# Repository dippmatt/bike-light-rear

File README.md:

# bike-light-rear

High-visibility rear bicycle light controlled from an ANT+ bike computer (ANT+ Bike Lights profile), featuring smart motion detection, ambient light sensing, and efficient single-cell Li-ion power management. Designed for hybrid assembly (pick-and-place for 0402/0603 passives, hand-soldering for connectors and high-value components).

## Hardware architecture

### Compute & wireless
- **BL653 module** (453-00039R) – Nordic nRF52833 SoC with integrated PCB trace antenna, ANT/Bluetooth radio, and 64 MHz Arm Cortex-M4F (the firmware uses the ANT SoftDevice, so the radio runs ANT+)
- **Programming** – 2×3 1.27mm SWD header for firmware flashing and debugging
- **System power** – 2.7V from NPM1100 buck regulator optimized for 90-95% battery capacity utilization (3.11V cutoff)

### Sensors (I2C bus @ 2.7V)
- **LIS3DH accelerometer** – 3-axis motion detection (braking / fall detection) for brake/acceleration events, configurable thresholds, interrupt-driven
- **OPT3001 light sensor** – 0.01-83k lux range with human-eye spectral matching for automatic brightness control and day/night mode switching

### High-power LED driver
- **Cree XP-E2** (XPEBRD-L1-0000-00801) – 625nm Red emitter driven at 500mA via PAM2804 step-down constant-current driver
- **Control** – PWM dimming via BL653 GPIO with 100kΩ pull-down for safe default-off state

### Power subsystem
- **Battery** – Single 18350 Li-ion cell (Vapcell 1100mAh, unprotected), 3.11-4.2V operating range
- **Charging** – USB-C PD sink (5.1kΩ CC resistors), NPM1100 linear charger @ 400mA (0Ω ICHG resistor), 4.2V termination
- **Protection** – DW01A IC with dual AO3400A N-channel MOSFETs (drain-to-drain configuration) for over-voltage (4.3V), under-voltage (2.5V), and over-current (>2A) protection
- **Buck regulator** – NPM1100 internal 2.7V @ 150mA output
- **Status monitoring** – CHG and ERR signals routed to BL653 GPIO for firmware-based charge status indication
- **NTC disable** – Thermal monitoring disabled via 10kΩ resistor from NTC pin to AVSS (GND)

### PCB specifications
- **Design tool** – KiCad 9.0 (schema version `20250114`)
- **Test points** – Critical nets labeled for bring-up and debugging (+BATT, +VSYS, +VDD_nRF, GND, I2C_SDA, I2C_SCL)

### Hardware photos

Assembled PCB on the 18350 battery holder (angled view).

Top of the populated PCB: BL653 (nRF52833), USB-C, tactile switch, RGB status LED, SWD header (J2), and I2C test point pads for the accelerometer and ambient light sensor.

Front of the 3D-printed enclosure with the Cree red main LED and status indicator.

Side of the enclosure showing the USB charge port.

## Repository layout
- `hardware/` – KiCad project, fabrication-toolkit config, custom libs (`kicad_symbols/`, `kicad_footprints/`, `kicad_3d_models/`), datasheets (markdown format), and generated BOM
- `software/rear_light_ant/` – rear light firmware (bare metal on the ANT SoftDevice S212), including Smart Mode, ANT+ bike light control, charging/idle state, and low-power sleep
- `software/rear_light_peripheral/` – the previous Zephyr/BLE rear light firmware, kept as reference until the physical checks of the ANT+ firmware are done
- `software/front_light_central/` – proof-of-concept BLE central/front-light firmware (experimental). It controlled the BLE rear light and does not work with the ANT+ rear light
- `software/` *(other folders)* – development history and experiments (central/peripheral prototypes, refactors, test projects)
- `docs/` – photos, rendered schematics, mechanical notes, and user-facing manuals
- `LICENSE` – GPLv3 with NonCommercial clause

## Hardware workflow
1. Install KiCad 9.0 or newer.
2. Install the [JLCPCB Fabrication Toolkit](https://github.com/bennymeg/Fabrication-Toolkit) to be able to export the design in the correct format for JLCPCBs [Design For Manufacturing (DFM) Tool](https://jlcdfm.com/).
3. Open `hardware/kicad_project/RearLight.kicad_pro` to access the schematic and PCB.
4. Run ERC/DRC before layout edits; generated artifacts (Gerbers, pick-and-place, STEP export) go to `hardware/kicad_project/production`, which is gitignored and intentionally kept out of releases.
5. Note: Components marked DNP (Do Not Populate) in fabrication files are intended for hand-soldering to minimize assembly costs.

## Firmware

The rear light firmware (`software/rear_light_ant/`) runs bare metal on the **ANT SoftDevice S212 7.0.1** of the **nRF52833 (BL653 module)**. ANT SoftDevices are not supported by Zephyr or the nRF Connect SDK, so it uses a plain Makefile with the compiler of an nRF Connect SDK toolchain installation (v3.1.1) and the register headers of its nrfx. It implements the lighting control with three light modes and is controlled by an ANT+ bike computer through the ANT+ Bike Lights profile (tested with a Wahoo ELEMNT BOLT v2).

### Features
- **Three light modes**: Steady, Flash (double flash) and Smart, plus Off from the bike computer
- **Smart Mode**: Adaptive brightness based on braking detection and ambient light
- **Braking Detection**: Automatic peak brightness boost during deceleration
- **Ambient Light Sensing**: Adjusts brightness for day/night conditions
- **Parking and auto-on**: when the bike stands still for 2.5 minutes Smart parks (LED off, short status pulse) and switches itself back on when the bike moves
- **Power Management**: Low-battery indication and automatic shut-off at low voltage, USB-C charging indication
- **ANT+ control**: state, battery and mode of the light on the bike computer, mode changes from the bike computer

For complete operating instructions and technical details, see the **[Rear light User Manual](software/rear_light_ant/MANUAL.md)**; the behaviour is specified in [SPEC.md](software/rear_light_ant/SPEC.md).

The **front light** uses the same board with a white LED and the same firmware source, built as a variant (`make LIGHT=front`): Smart, Standard (30 %) and Bright (80 %), see the **[Front light User Manual](software/rear_light_ant/MANUAL_FRONT.md)**. The BLE front light firmware in `software/front_light_central/` is superseded.

### Firmware environment setup
1. Install the [nRF Command Line Tools](https://www.nordicsemi.com/Products/Development-tools/nrf-command-line-tools) for access to `nrfjprog` and a J-Link.
2. Install the **nRF Connect SDK toolchain v3.1.1** (nRF Connect for VS Code, Toolchain Manager). Only its GNU Arm compiler and the nrfx register headers are used.
3. Put the ANT SoftDevice archive `ANT_s212_nrf52_7.0.1.zip` (from the Garmin/ANT downloads) into `software/ant_source/SoftDevices_Current_Items/`. The folder is gitignored: the ANT+ documents and SoftDevice files must not be redistributed.
4. `cd software/rear_light_ant && make test && make flash` (front light: `make LIGHT=front flash`; see its [README](software/rear_light_ant/README.md) for options, bench tools and the licence key).

The previous Zephyr firmware in `software/rear_light_peripheral/` is built with the nRF Connect for VS Code extension as before (nRF Connect Bare Metal SDK v0.9.0 and toolchain v3.1.1).

Note 1: Device flashing using WSL2  
To connect a J-Link debugger to a WSL instance:
- Open a Windows PowerShell terminal and run:
- `usbipd list`
- `usbipd bind --busid <J-Link BusID>`
- `usbipd attach --wsl --busid <J-Link BusID>`

Note 2: Device does not show up under “Connected Devices” in the nRF Connect VS Code extension
- Install [nRF-Util](https://www.nordicsemi.com/Products/Development-tools/nRF-Util)
- Make nrfutil executable using `chmod +x nrfutil`
- Move the nrfutil executable to a directory in the system $PATH (e.g. /usr/bin)
- Install the _device_ package for nrfutil using `nrfutil install device`
- Restart VSCode. Your device should now show up under _Connected Devices_ in nRF Connect  

## License
This hardware is released under **GPLv3 + NonCommercial**. You may copy, modify, and share for non-commercial use as long as derivatives retain the same license and attribution. See `LICENSE` for full terms.

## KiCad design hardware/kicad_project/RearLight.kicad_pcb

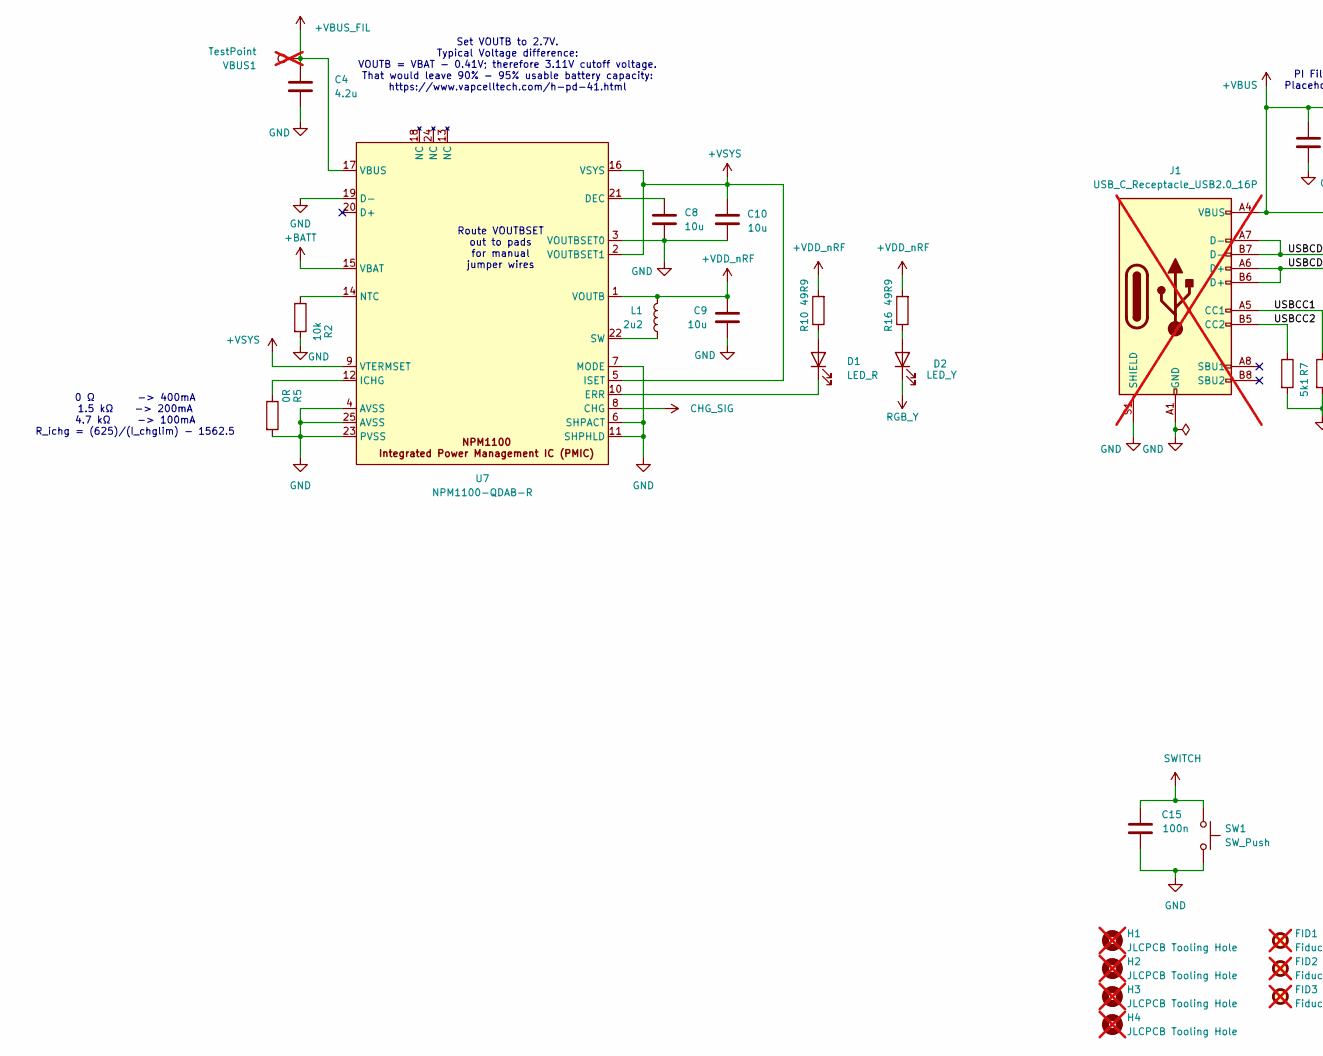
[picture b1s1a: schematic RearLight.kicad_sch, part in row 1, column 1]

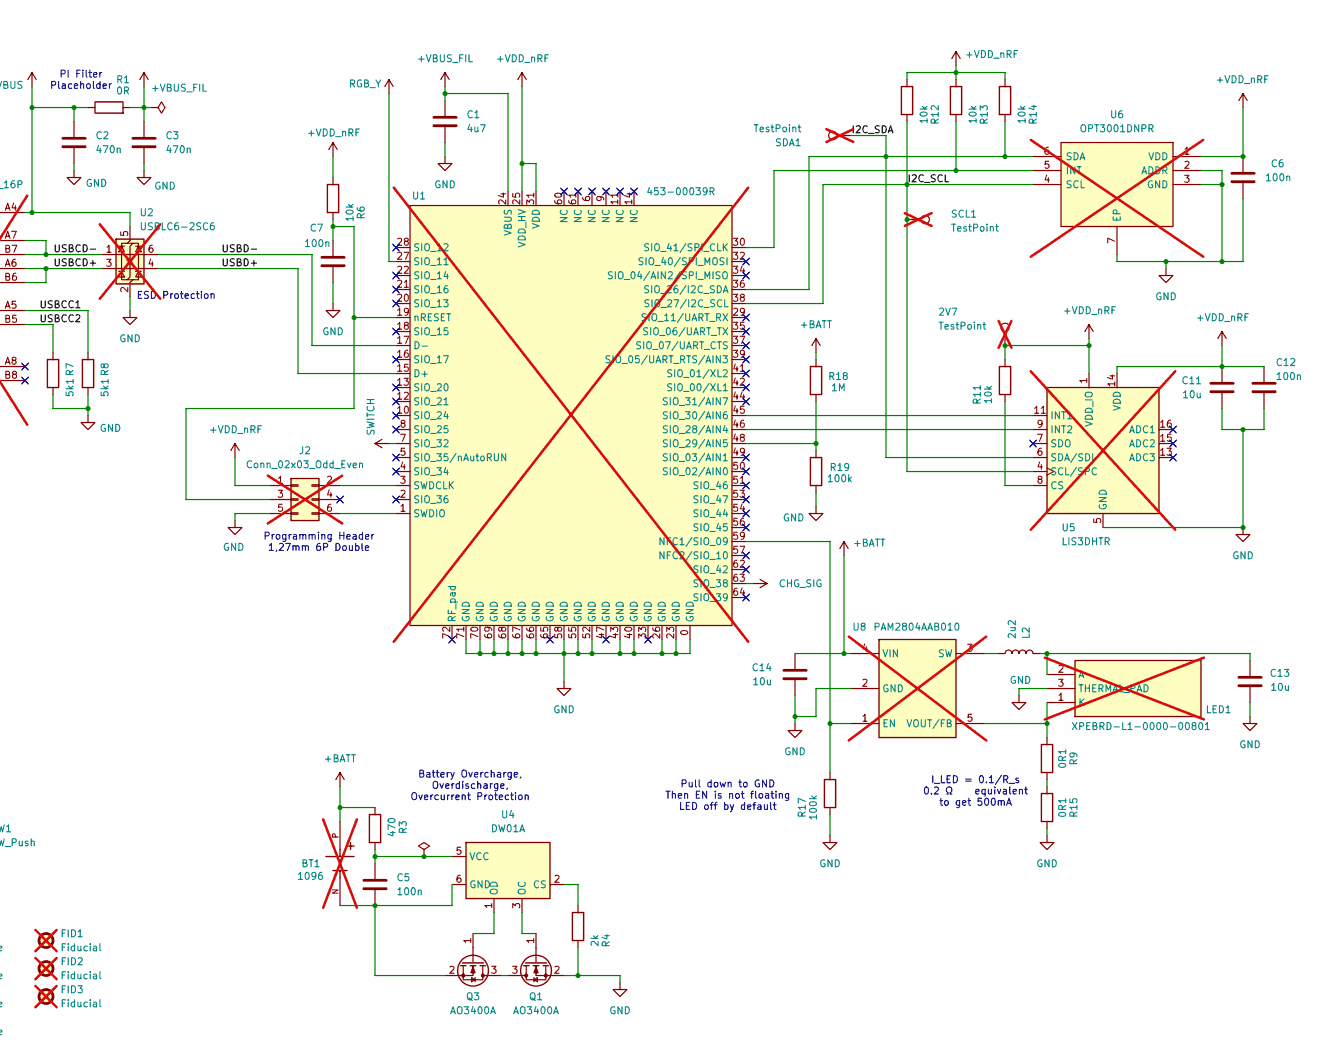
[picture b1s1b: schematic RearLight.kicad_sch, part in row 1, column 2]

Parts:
2V7: TestPoint; TestPoint_Pad_D1.0mm; not fitted
BT1: 1096; BAT_1096_holes_slim; PARTREV A; DigiKey_Part_Number 36-1096-ND; not fitted
C1: 4u7; C_0805_2012Metric; LCSC C1779
C2, C3: 470n; C_0603_1608Metric_NO_SILK; LCSC C1623
C4: 4.2u; C_0805_2012Metric; LCSC C377773
C5, C6, C7, C12, C15: 100n; C_0805_2012Metric; LCSC C28233
C8, C9, C10, C11, C13, C14: 10u; C_0805_2012Metric; LCSC C15850
D1: LED_R; LED_0603_1608Metric; LCSC C2286
D2: LED_Y; LED_0805_2012Metric; LCSC C2296
FID1, FID2, FID3: Fiducial; Fiducial_1mm_Mask2mm; not fitted
H1, H2, H3, H4: JLCPCB Tooling Hole; ToolingHole_1.152mm; not fitted
J1: USB_C_Receptacle_USB2.0_16P; USB_C_Receptacle_GCT_USB4105-xx-A_16P_TopMnt_Horizontal_wid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; Manufacturer Part Number USB4105-GF-A-060; LCSC C3025063; not fitted
J2: Conn_02x03_Odd_Even; PinHeader_2x03_P1.27mm_Vertical; not fitted
L1, L2: 2u2; L_0805_2012Metric; LCSC C1043
LED1: XPEBRD-L1-0000-00801; XPEWHTL1000000E01; Manufacturer_Part_Number XPEBRD-L1-0000-00801; LCSC C5364087; not fitted
Q1, Q3: AO3400A; SOT-23; LCSC C20917
R1, R5: 0R; R_0603_1608Metric_NO_SILK; LCSC C21189
R2, R6, R12, R13, R14: 10k; R_0402_1005Metric_NO_SILK; Manufacturer Part Number 0402WGF1002TCE; LCSC C25744
R3: 470; R_0402_1005Metric_NO_SILK; Manufacturer Part Number 0402WGF4700TCE; LCSC C25117
R4: 2k; R_0402_1005Metric_NO_SILK; Manufacturer Part Number 0402WGF2001TCE; LCSC C4109
R7, R8: 5k1; R_0402_1005Metric_NO_SILK; Manufacturer Part Number 0402WGF5101TCE; LCSC C25905
R9, R15: 0R1; R_1206_3216Metric; Manufacturer Part Number 1206W4F100LT5E; LCSC C25334
R10, R16: 49R9; R_0402_1005Metric_NO_SILK; Manufacturer Part Number 0402WGF499JTCE; LCSC C25120
R11: 10k; R_0603_1608Metric_NO_SILK; Manufacturer Part Number 0603WAF1002T5E; LCSC C25804
R17, R19: 100k; R_0402_1005Metric_NO_SILK; Manufacturer Part Number 0402WGF1003TCE; LCSC C25741
R18: 1M; R_0402_1005Metric_NO_SILK; Manufacturer Part Number 0402WGF1004TCE; LCSC C26083
SCL1: TestPoint; TestPoint_Pad_D1.0mm; not fitted
SDA1: TestPoint; TestPoint_Pad_D1.0mm; not fitted
SW1: SW_Push; SW_TS-1088-AR02016; LCSC C720477
U1: 453-00039R; Laird_BL653; LCSC C6421506; not fitted
U2: USBLC6-2SC6; SOT-23-6; Manufacturer Part Number USBLC6-2SC6; LCSC C7519; not fitted
U4: DW01A; SOT-23-6; LCSC C18164398
U5: LIS3DHTR; LGA-16_3x3mm_P0.5mm_LayoutBorder3x5y; Manufacturer Part Number LIS3DHTR; LCSC C15134; not fitted
U6: OPT3001DNPR; SON65P200X200X65-7N-D; Mouser Part Number 595-OPT3001DNPR; not fitted
U7: NPM1100-QDAB-R; QFN50P400X400X90-25N-D; LCSC C5833729
U8: PAM2804AAB010; SOT95P280X100-5N; LCSC C71463; not fitted
VBUS1: TestPoint; TestPoint_Pad_D1.0mm; not fitted

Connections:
+BATT: BT1.P, C14.1, R3.1, R18.1, U7.15 (VBAT), U8.4 (VIN)
+VBUS: C2.1, J1.A4 (VBUS), J1.A9 (VBUS), J1.B4 (VBUS), J1.B9 (VBUS), R1.1, U2.5 (VBUS)
+VBUS_FIL: C1.1, C3.1, C4.1, R1.2, U1.24 (VBUS), U7.17 (VBUS), VBUS1.1
+VDD_nRF: 2V7.1, C6.1, C9.1, C11.1, C12.1, J2.1, L1.1, R6.1, R10.2, R11.1, R12.1, R13.1, R14.1, R16.2, U1.25 (VDD_HV), U1.31 (VDD), U5.1 (VDD_IO), U5.14 (VDD), U6.1 (VDD), U7.1 (VOUTB)
+VSYS: C10.1, U7.2 (VOUTBSET1), U7.5 (ISET), U7.9 (VTERMSET), U7.16 (VSYS)
/I2C_SCL: R12.2, SCL1.1, U1.38 (SIO_27/I2C_SCL), U5.4 (SCL/SPC), U6.4 (SCL)
/I2C_SDA: R14.2, SDA1.1, U1.36 (SIO_26/I2C_SDA), U5.6 (SDA/SDI), U6.6 (SDA)
/USBCC1: J1.A5 (CC1), R8.1
/USBCC2: J1.B5 (CC2), R7.1
/USBCD+: J1.A6 (D+), J1.B6 (D+), U2.3 (I/O2)
/USBCD-: J1.A7 (D-), J1.B7 (D-), U2.1 (I/O1)
/USBD+: U1.15 (D+), U2.4 (I/O2)
/USBD-: U1.17 (D-), U2.6 (I/O1)
CHG_SIG: U1.63 (SIO_38), U7.8 (CHG)
GND: C1.2, C2.2, C3.2, C4.2, C6.2, C7.2, C8.2, C9.2, C10.2, C11.2, C12.2, C13.2, C14.2, C15.2, J1.A1 (GND), J1.A12 (GND), J1.B1 (GND), J1.B12 (GND), J1.S1 (SHIELD), J2.5, LED1.3 (THERMAL_PAD), Q1.2 (S), R2.2, R4.2, R5.2, R7.2, R8.2, R15.2, R17.2, R19.2, SW1.2, U1.0 (GND), U1.23 (GND), U1.26 (GND), U1.40 (GND), U1.43 (GND), U1.52 (GND), U1.55 (GND), U1.58 (GND), U1.66 (GND), U1.67 (GND), U1.68 (GND), U1.69 (GND), U1.70 (GND), U1.71 (GND), U2.2 (GND), U5.5 (GND), U5.10 (GND), U5.12 (GND), U6.2 (ADDR), U6.3 (GND), U6.7 (EP), U7.3 (VOUTBSET0), U7.4 (AVSS), U7.6 (SHPACT), U7.7 (MODE), U7.11 (SHPHLD), U7.19 (D-), U7.23 (PVSS), U7.25 (AVSS), U8.2 (GND)
unnamed: D1.2 (A), R10.1
unnamed: D1.1 (K), U7.10 (ERR)
unnamed: D2.2 (A), R16.1
unnamed: J2.2, U1.3 (SWDCLK)
unnamed: C7.1, J2.3, R6.2, U1.19 (nRESET)
unnamed: J2.6, U1.1 (SWDIO)
unnamed: C13.1, L2.1, LED1.2 (A)
unnamed: LED1.1 (K), R9.1, U8.5 (VOUT/FB)
unnamed: Q1.3 (D), Q3.3 (D)
unnamed: Q1.1 (G), U4.3 (OC)
unnamed: Q3.1 (G), U4.1 (OD)
unnamed: BT1.N, C5.2, Q3.2 (S), U4.6 (GND)
unnamed: R9.2, R15.1
unnamed: R17.1, U1.59 (NFC1/SIO_09), U8.1 (EN)
unnamed: U1.46 (SIO_28/AIN4), U5.9 (INT2)
unnamed: R18.2, R19.1, U1.48 (SIO_29/AIN5)
unnamed: U1.45 (SIO_30/AIN6), U5.11 (INT1)
unnamed: R13.2, U1.30 (SIO_41/SPI_CLK), U6.5 (INT)
unnamed: R4.1, U4.2 (CS)
unnamed: C5.1, R3.2, U4.5 (VCC)
unnamed: R11.2, U5.8 (CS)
unnamed: C8.1, U7.21 (DEC)
unnamed: R5.1, U7.12 (ICHG)
unnamed: R2.1, U7.14 (NTC)
unnamed: L1.2, U7.22 (SW)
unnamed: L2.2, U8.3 (SW)
RGB_Y: D2.1 (K), U1.27 (SIO_11)
SWITCH: C15.1, SW1.1, U1.7 (SIO_32)

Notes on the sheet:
0 Ω -> 400mA 1.5 kΩ -> 200mA 4.7 kΩ -> 100mA R_ichg = (625)/(I_chglim) - 1562.5
Programming Header 1,27mm 6P Double
Set VOUTB to 2.7V. Typical Voltage difference: VOUTB = VBAT - 0.41V; therefore 3.11V cutoff voltage. That would leave 90% - 95% usable battery capacity: https://www.vapcelltech.com/h-pd-41.html
Route VOUTBSET out to pads for manual jumper wires
ESD Protection
I_LED = 0.1/R_s 0.2 Ω equivalent to get 500mA
PI Filter Placeholder
Pull down to GND Then EN is not floating LED off by default
Battery Overcharge, Overdischarge, Overcurrent Protection

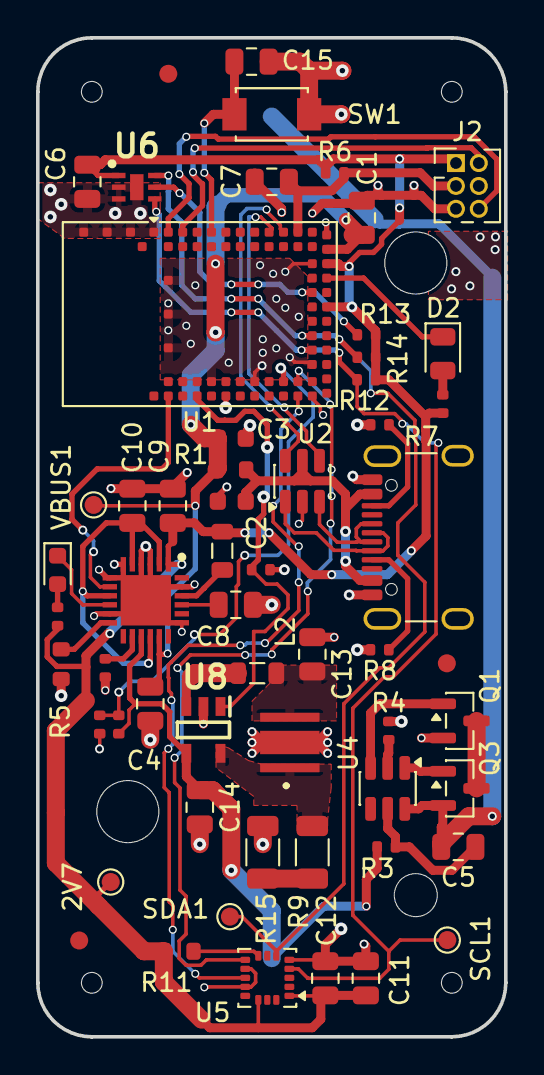
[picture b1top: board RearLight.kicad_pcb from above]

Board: 2 copper layers, 26.0 x 55.5 mm, 63 parts (1 on the bottom side), 43 nets.

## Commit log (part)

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2025-11-07 Added kicad project (schematic)
2025-11-08 Schematic first draft, review needed
2025-11-15 Schematic done; Layout first draft
2025-11-18 Layout 2nd draft
    Todo: increase via size
2025-11-18 DFM design overhaul
2025-11-19 Broad hardware documentation in readme
2025-11-19 Added correct tooling holes for JLCPCB assembly
2025-11-19 better placement & silkscreen for DFM
2025-11-19 Added total cost calculation spredsheet
2025-11-19 Added 100k pulldown to LED driver EN
2025-11-20 Production Version 1.0
    Moved red LED to NPM1100
2025-11-21 Updated actual cost of oredered parts.
2025-12-11 updated board thickness to 1.6 mm
    The board was manufactured with 1.6 mm board thickness accidentaly.
    To reflect this, updated the kicad project as well.
2025-12-23 Initial nRF Connect software setup
2025-12-24 Simple LED on/off control w/ 50% PWM duty cycle
2025-12-24 3-mode light toggle: off, 50%, 100%
2025-12-25 Refactor & Add strict compiler warnings
    - Moved button_control functionallity to main.
    - Enable -Wall, -Wextra, and -Werror for stricter code quality
    - Link math library (-lm) for future sensor calculations
2025-12-25 Added temperature sensor
2025-12-27 Added accellerometer sensor
2025-12-27 Added DEBUG parameter to exclude printing
2025-12-27 Fixed too fast PWM frequency
    100us period got filtered out by the series inductor with the power LED
    1ms period is appropriate for dimming functions.
2025-12-27 Updated license headers
2025-12-31 Added braking and low ambient light detection.
2026-01-04 Added Sleep mode & Smart mode
    Sleep mode uses ~20 uA (device off) w/ wake button interrupt.
    Smart Mode controls the led brightness based on braking deceleration & abient light.
2026-01-04 Code refactored for structure
2026-01-08 Refactored state machine
2026-01-08 Code simplification according to comments attached
    MAIN.C
    Constant definitions
    - Get the status led integer definition from DT
    X - Set the PWM width for the Status Led to 500ms --> rename TIMER_INTERVAL_MS to STATUS_TIMER_INTERVAL
    - Get the device tree specifications (pointer to gpio_dt_spec) from the status led
    X - Define a k_timer led_timer for the status led --> rename to status_led_timer
2026-01-09 Added double flash to flash mode
2026-01-16 Added first bluetooth sync function
2026-01-16 Added short and long press detection
2026-01-21 State machine to OFF after 10s of button inactivity
2026-01-26 Non working BLE setup
2026-01-26 Integrated seperate bluetooth central & peripheral applications
2026-01-30 Added correct BLE functionality
    A bug that prevents the peripheral to enter sleep mode after smart mode exists
    This bug is there after the first sleep cycle. Something is not configured correctly.
2026-02-08 fixed script to add submodules as files
2026-02-08 Several Fixes
    sensor_data_collector.c -- 5 fixes:
    Busy-loop fix: Added k_sleep(K_SECONDS(150)) before continue in stationary monitor
    Integer math: Replaced double + sqrt() with sensor_value_to_milli() + squared-magnitude comparison, removed <math.h>
    Atomic flag: sensor_sampling_active changed from bool to atomic_t
    Stack sizes: Both thread stacks increased from 1024 to 2048
    Zero-init: sensor_readings_t value now = {0} to avoid uninitialized reads
2026-02-15 Fixed double press-off
2026-02-15 Removed startup timer doing nothing
2026-02-15 Added adc readings of battery voltage
2026-02-15 Auto shut-off below 3V; low battery indication below 3.4V
2026-05-19 Added status LED low battery indicator (blinking)
2026-05-19 Added photos to README
